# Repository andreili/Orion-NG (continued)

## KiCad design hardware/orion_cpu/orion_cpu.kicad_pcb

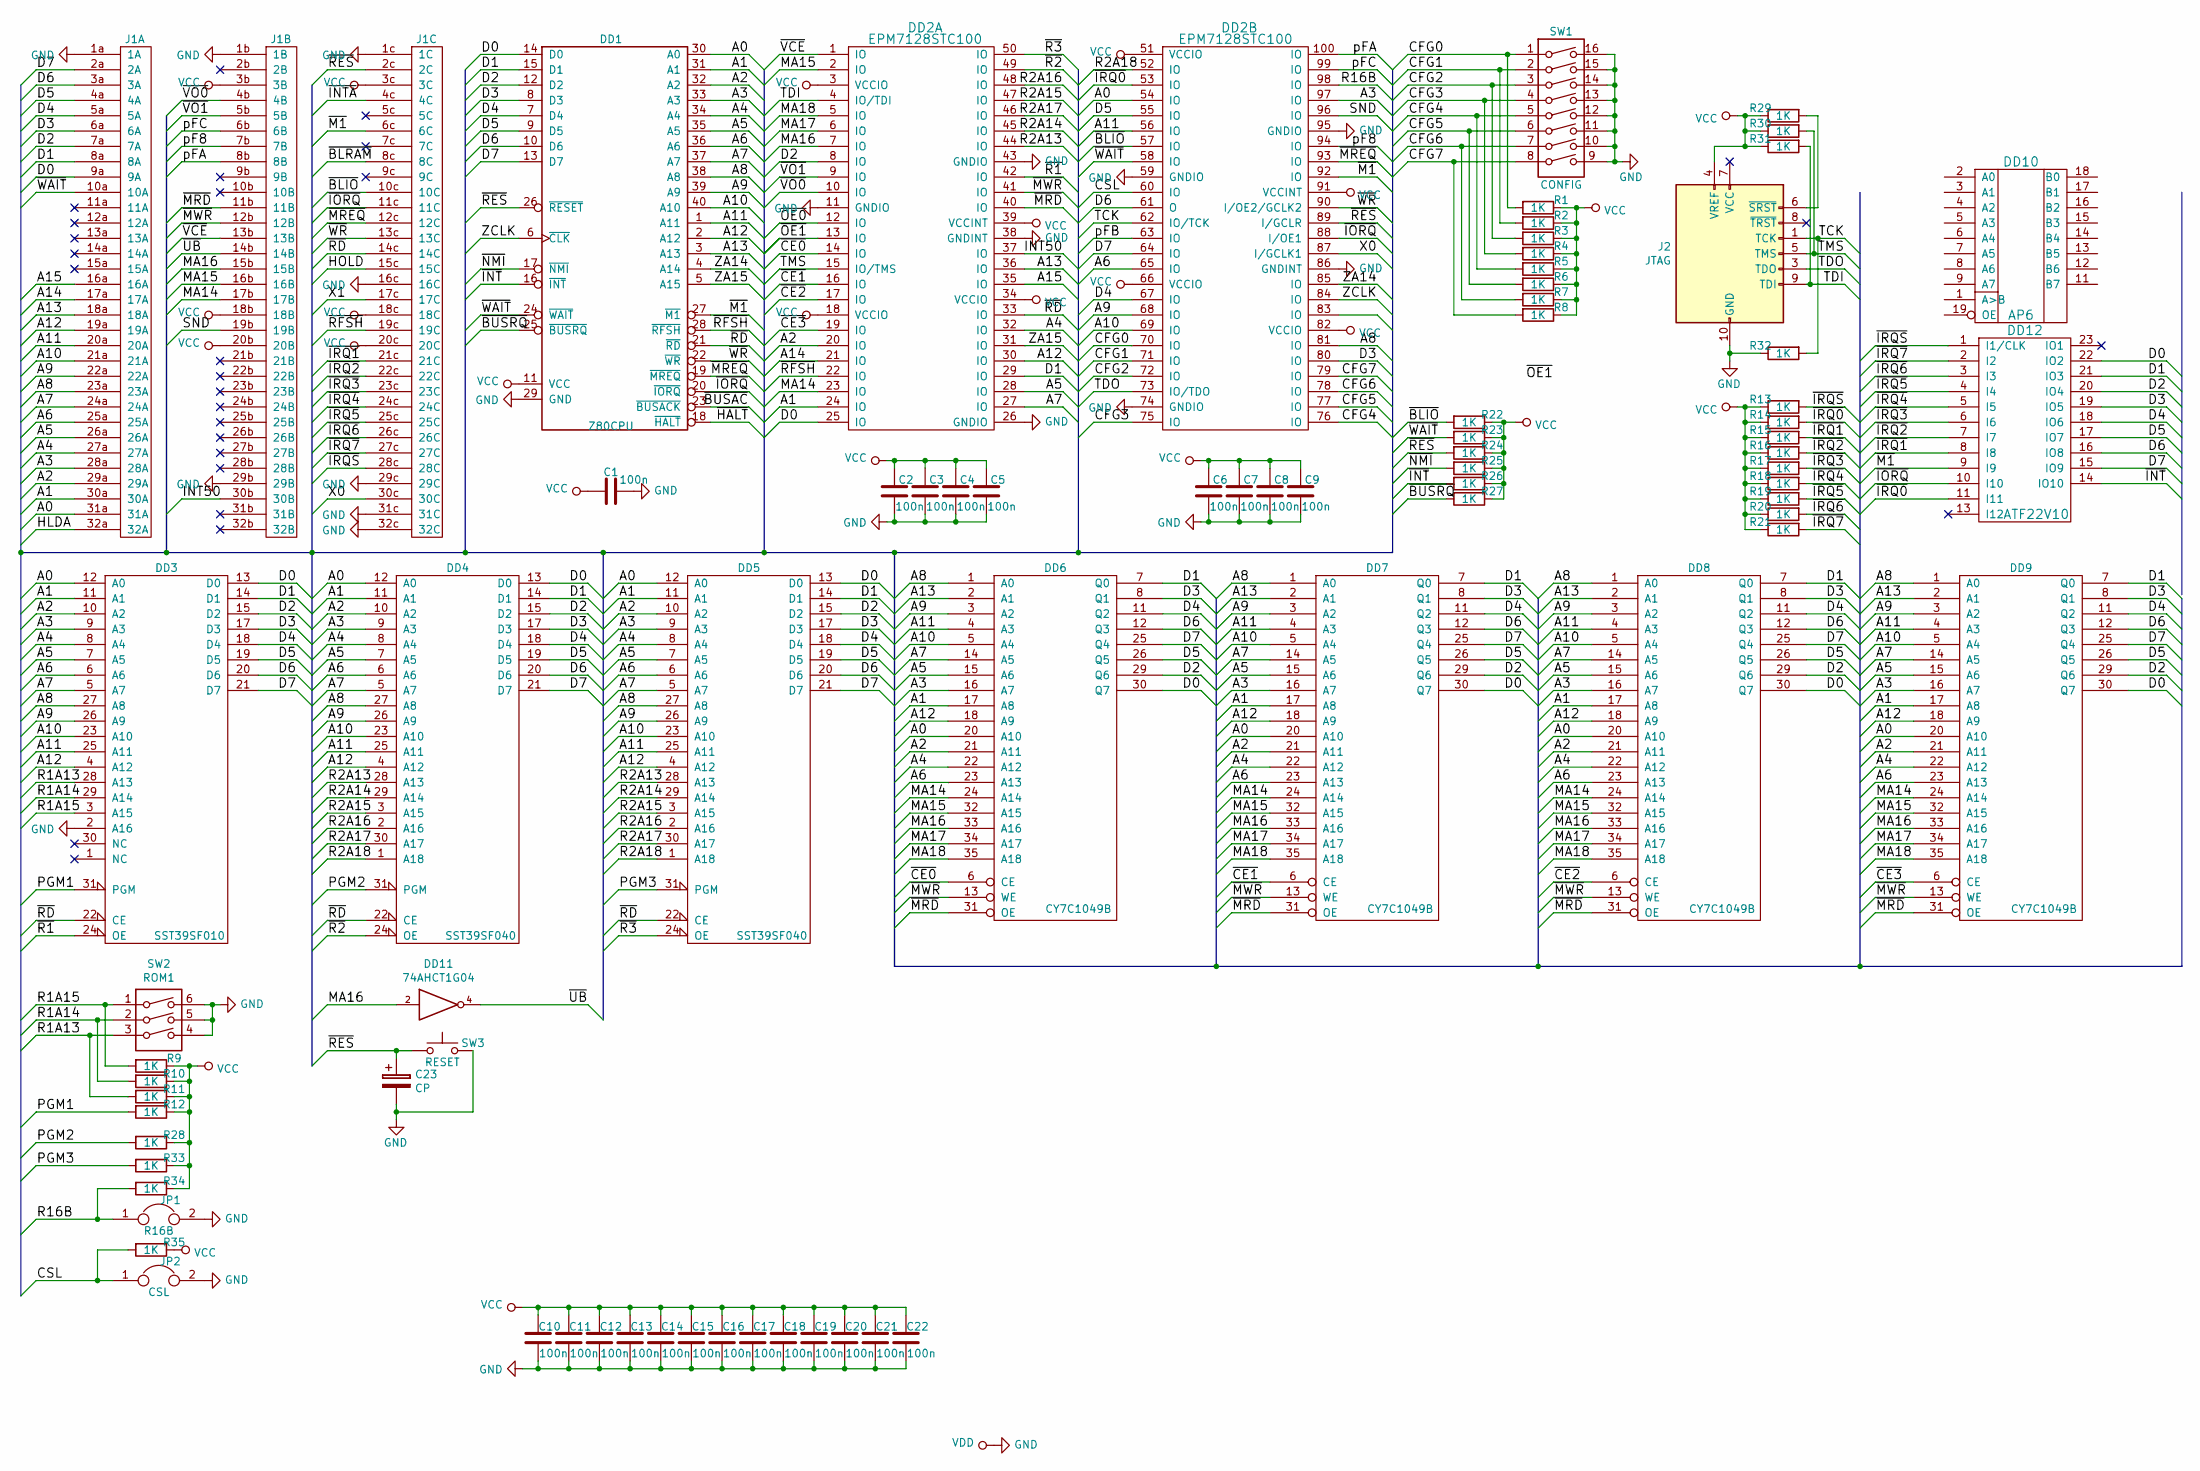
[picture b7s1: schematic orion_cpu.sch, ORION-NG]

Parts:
C1, C2, C3, C4, C5, C6, C7, C8, C9, C10, C11, C12, C13, C14, C15, C16, C17, C18, C19, C20, C21, C22: 100n; C_0805_2012Metric
C23: CP; CP_Tantalum_Case-A_EIA-3216-18_Hand
DD1: Z80CPU; DIP-40_W15.24mm_Socket
DD2: EPM7128STC100; LQFP-100_14x14mm_P0.5mm
DD3: SST39SF010; plcc32_pth-skt
DD4, DD5: SST39SF040; plcc32_pth-skt
DD6, DD7, DD8, DD9: CY7C1049B; SOJ-36
DD10: AP6; SOIC-20W_7.5x12.8mm_P1.27mm
DD11: 74AHCT1G04; SOT-353_SC-70-5_Handsoldering
DD12: ATF22V10; DIP-24_W7.62mm_Socket
J1: C96ABC; Socket_DIN41612-CaseC1-full-Male-96Pin-3rows
J2: JTAG; PinHeader_2x05_P2.54mm_Vertical
JP1: R16B; Pin_Header_Straight_1x02_Pitch2.54mm
JP2: CSL; Pin_Header_Straight_1x02_Pitch2.54mm
R1, R2, R3, R4, R5, R6, R7, R8, R9, R10, R11, R12, R13, R14, R15, R16, R17, R18, R19, R20, R21, R22, R23, R24, R25, R26, R27, R28, R29, R30, R31, R32, R33, R34, R35: 1K; R_0805_2012Metric
SW1: CONFIG; SW_DIP_SPSTx08_Slide_9.78x22.5mm_W7.62mm_P2.54mm
SW2: ROM1; SW_DIP_SPSTx03_Slide_9.78x9.8mm_W7.62mm_P2.54mm
SW3: RESET; SW_Tactile_SPST_Angled_PTS645Vx83-2LFS

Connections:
/A0: DD1.30 (A0), DD2.54 (IO), DD3.12 (A0), DD4.12 (A0), DD5.12 (A0), DD6.20 (A10), DD7.20 (A10), DD8.20 (A10), DD9.20 (A10), J1.31a (31A)
/A1: DD1.31 (A1), DD2.24 (IO), DD3.11 (A1), DD4.11 (A1), DD5.11 (A1), DD6.17 (A8), DD7.17 (A8), DD8.17 (A8), DD9.17 (A8), J1.30a (30A)
/A2: DD1.32 (A2), DD2.20 (IO), DD3.10 (A2), DD4.10 (A2), DD5.10 (A2), DD6.21 (A11), DD7.21 (A11), DD8.21 (A11), DD9.21 (A11), J1.29a (29A)
/A3: DD1.33 (A3), DD2.97 (IO), DD3.9 (A3), DD4.9 (A3), DD5.9 (A3), DD6.16 (A7), DD7.16 (A7), DD8.16 (A7), DD9.16 (A7), J1.28a (28A)
/A4: DD1.34 (A4), DD2.32 (IO), DD3.8 (A4), DD4.8 (A4), DD5.8 (A4), DD6.22 (A12), DD7.22 (A12), DD8.22 (A12), DD9.22 (A12), J1.27a (27A)
/A5: DD1.35 (A5), DD2.28 (IO), DD3.7 (A5), DD4.7 (A5), DD5.7 (A5), DD6.15 (A6), DD7.15 (A6), DD8.15 (A6), DD9.15 (A6), J1.26a (26A)
/A6: DD1.36 (A6), DD2.65 (IO), DD3.6 (A6), DD4.6 (A6), DD5.6 (A6), DD6.23 (A13), DD7.23 (A13), DD8.23 (A13), DD9.23 (A13), J1.25a (25A)
/A7: DD1.37 (A7), DD2.27 (IO), DD3.5 (A7), DD4.5 (A7), DD5.5 (A7), DD6.14 (A5), DD7.14 (A5), DD8.14 (A5), DD9.14 (A5), J1.24a (24A)
/A8: DD1.38 (A8), DD2.81 (IO), DD3.27 (A8), DD4.27 (A8), DD5.27 (A8), DD6.1 (A0), DD7.1 (A0), DD8.1 (A0), DD9.1 (A0), J1.23a (23A)
/A9: DD1.39 (A9), DD2.68 (IO), DD3.26 (A9), DD4.26 (A9), DD5.26 (A9), DD6.3 (A2), DD7.3 (A2), DD8.3 (A2), DD9.3 (A2), J1.22a (22A)
/A10: DD1.40 (A10), DD2.69 (IO), DD3.23 (A10), DD4.23 (A10), DD5.23 (A10), DD6.5 (A4), DD7.5 (A4), DD8.5 (A4), DD9.5 (A4), J1.21a (21A)
/A11: DD1.1 (A11), DD2.56 (IO), DD3.25 (A11), DD4.25 (A11), DD5.25 (A11), DD6.4 (A3), DD7.4 (A3), DD8.4 (A3), DD9.4 (A3), J1.20a (20A)
/A12: DD1.2 (A12), DD2.30 (IO), DD3.4 (A12), DD4.4 (A12), DD5.4 (A12), DD6.18 (A9), DD7.18 (A9), DD8.18 (A9), DD9.18 (A9), J1.19a (19A)
/A13: DD1.3 (A13), DD2.36 (IO), DD6.2 (A1), DD7.2 (A1), DD8.2 (A1), DD9.2 (A1), J1.18a (18A)
/A14: DD2.21 (IO), J1.17a (17A)
/A15: DD2.35 (IO), J1.16a (16A)
/CFG0: DD2.70 (IO), R1.2, SW1.1
/CFG1: DD2.71 (IO), R2.2, SW1.2
/CFG2: DD2.72 (IO), R3.2, SW1.3
/CFG3: DD2.75 (IO), R4.2, SW1.4
/CFG4: DD2.76 (IO), R5.2, SW1.5
/CFG5: DD2.77 (IO), R6.2, SW1.6
/CFG6: DD2.78 (IO), R7.2, SW1.7
/CFG7: DD2.79 (IO), R8.2, SW1.8
/CSL: DD2.60 (IO), JP2.1, R35.2
/D0: DD1.14 (D0), DD2.25 (IO), DD3.13 (D0), DD4.13 (D0), DD5.13 (D0), DD6.30 (Q7), DD7.30 (Q7), DD8.30 (Q7), DD9.30 (Q7), DD12.22 (IO2), J1.9a (9A)
/D1: DD1.15 (D1), DD2.29 (IO), DD3.14 (D1), DD4.14 (D1), DD5.14 (D1), DD6.7 (Q0), DD7.7 (Q0), DD8.7 (Q0), DD9.7 (Q0), DD12.21 (IO3), J1.8a (8A)
/D2: DD1.12 (D2), DD2.8 (IO), DD3.15 (D2), DD4.15 (D2), DD5.15 (D2), DD6.29 (Q6), DD7.29 (Q6), DD8.29 (Q6), DD9.29 (Q6), DD12.20 (IO4), J1.7a (7A)
/D3: DD1.8 (D3), DD2.80 (IO), DD3.17 (D3), DD4.17 (D3), DD5.17 (D3), DD6.8 (Q1), DD7.8 (Q1), DD8.8 (Q1), DD9.8 (Q1), DD12.19 (IO5), J1.6a (6A)
/D4: DD1.7 (D4), DD2.67 (IO), DD3.18 (D4), DD4.18 (D4), DD5.18 (D4), DD6.11 (Q2), DD7.11 (Q2), DD8.11 (Q2), DD9.11 (Q2), DD12.18 (IO6), J1.5a (5A)
/D5: DD1.9 (D5), DD2.55 (IO), DD3.19 (D5), DD4.19 (D5), DD5.19 (D5), DD6.26 (Q5), DD7.26 (Q5), DD8.26 (Q5), DD9.26 (Q5), DD12.17 (IO7), J1.4a (4A)
/D6: DD1.10 (D6), DD2.61 (O), DD3.20 (D6), DD4.20 (D6), DD5.20 (D6), DD6.12 (Q3), DD7.12 (Q3), DD8.12 (Q3), DD9.12 (Q3), DD12.16 (IO8), J1.3a (3A)
/D7: DD1.13 (D7), DD2.64 (IO), DD3.21 (D7), DD4.21 (D7), DD5.21 (D7), DD6.25 (Q4), DD7.25 (Q4), DD8.25 (Q4), DD9.25 (Q4), DD12.15 (IO9), J1.2a (2A)
/HLDA: J1.32a (32A)
/HOLD: J1.15c (15C)
/INT50: DD2.37 (IO), J1.30b (30B)
/MA14: DD2.23 (IO), DD6.24 (A14), DD7.24 (A14), DD8.24 (A14), DD9.24 (A14), J1.17b (17B)
/MA15: DD2.2 (IO), DD6.32 (A15), DD7.32 (A15), DD8.32 (A15), DD9.32 (A15), J1.16b (16B)
/MA16: DD2.7 (IO), DD6.33 (A16), DD7.33 (A16), DD8.33 (A16), DD9.33 (A16), DD11.2, J1.15b (15B)
/MA17: DD2.6 (IO), DD6.34 (A17), DD7.34 (A17), DD8.34 (A17), DD9.34 (A17)
/MA18: DD2.5 (IO), DD6.35 (A18), DD7.35 (A18), DD8.35 (A18), DD9.35 (A18)
/PGM1: DD3.31 (PGM), R12.2
/PGM2: DD4.31 (PGM), R28.2
/PGM3: DD5.31 (PGM), R33.2
/R1A13: DD3.28 (A13), R11.2, SW2.3
/R1A14: DD3.29 (A14), R10.2, SW2.2
/R1A15: DD3.3 (A15), R9.2, SW2.1
/R2A13: DD2.44 (IO), DD4.28 (A13), DD5.28 (A13)
/R2A14: DD2.45 (IO), DD4.29 (A14), DD5.29 (A14)
/R2A15: DD2.47 (IO), DD4.3 (A15), DD5.3 (A15)
/R2A16: DD2.48 (IO), DD4.2 (A16), DD5.2 (A16)
/R2A17: DD2.46 (IO), DD4.30 (A17), DD5.30 (A17)
/R2A18: DD2.52 (IO), DD4.1 (A18), DD5.1 (A18)
/R16B: DD2.98 (IO), JP1.1, R34.2
/SND: DD2.96 (IO), J1.19b (19B)
/TCK: DD2.62 (IO/TCK), J2.1 (TCK), R32.2
/TDI: DD2.4 (IO/TDI), J2.9 (TDI), R31.2
/TDO: DD2.73 (IO/TDO), J2.3 (TDO)
/TMS: DD2.15 (IO/TMS), J2.5 (TMS), R30.2
/X0: DD2.87 (I/GCLK1), J1.30c (30C)
/X1: J1.17c (17C)
/ZA14: DD1.4 (A14), DD2.85 (IO)
/ZA15: DD1.5 (A15), DD2.31 (IO)
/ZCLK: DD1.6 (~CLK~), DD2.84 (IO)
/pF8: DD2.94 (IO), J1.7b (7B)
/pFA: DD2.100 (IO), J1.8b (8B)
/pFB: DD2.63 (IO)
/pFC: DD2.99 (IO), J1.6b (6B)
/~BLIO: DD2.57 (IO), J1.10c (10C), R22.2
/~BLRAM: J1.8c (8C)
/~BUSAC: DD1.23 (~BUSACK~)
/~BUSRQ: DD1.25 (~BUSRQ~), R27.2
/~CE0: DD2.14 (IO), DD6.6 (CE)
/~CE1: DD2.16 (IO), DD7.6 (CE)
/~CE2: DD2.17 (IO), DD8.6 (CE)
/~CE3: DD2.19 (IO), DD9.6 (CE)
/~HALT: DD1.18 (~HALT~)
/~INT: DD1.16 (~INT~), DD12.14 (IO10), R26.2
/~INTA: J1.4c (4C)
/~IORQ: DD1.20 (~IORQ~), DD2.88 (I/OE1), DD12.10 (I10), J1.11c (11C)
/~IRQ0: DD2.53 (IO), DD12.11 (I11), R14.2
/~IRQ1: DD12.8 (I8), J1.21c (21C), R15.2
/~IRQ2: DD12.7 (I7), J1.22c (22C), R16.2
/~IRQ3: DD12.6 (I6), J1.23c (23C), R17.2
/~IRQ4: DD12.5 (I5), J1.24c (24C), R18.2
/~IRQ5: DD12.4 (I4), J1.25c (25C), R19.2
/~IRQ6: DD12.3 (I3), J1.26c (26C), R20.2
/~IRQ7: DD12.2 (I2), J1.27c (27C), R21.2
/~IRQS: DD12.1 (I1/CLK), J1.28c (28C), R13.2
/~M1: DD1.27 (~M1~), DD2.92 (IO), DD12.9 (I9), J1.6c (6C)
/~MRD: DD2.40 (IO), DD6.31 (OE), DD7.31 (OE), DD8.31 (OE), DD9.31 (OE), J1.11b (11B)
/~MREQ: DD1.19 (~MREQ~), DD2.93 (IO), J1.12c (12C)
/~MWR: DD2.41 (IO), DD6.13 (WE), DD7.13 (WE), DD8.13 (WE), DD9.13 (WE), J1.12b (12B)
/~NMI: DD1.17 (~NMI~), R25.2
/~OE0: DD2.12 (IO)
/~OE1: DD2.13 (IO)
/~R1: DD2.42 (IO), DD3.24 (OE)
/~R2: DD2.49 (IO), DD4.24 (OE)
/~R3: DD2.50 (IO), DD5.24 (OE)
/~RD: DD1.21 (~RD~), DD2.33 (IO), DD3.22 (CE), DD4.22 (CE), DD5.22 (CE), J1.14c (14C)
/~RES: C23.1, DD1.26 (~RESET~), DD2.89 (I/GCLR), J1.2c (2C), R24.2, SW3.2
/~RFSH: DD1.28 (~RFSH~), DD2.22 (IO), J1.19c (19C)
/~UB: DD11.4, J1.14b (14B)
/~VCE: DD2.1 (IO), J1.13b (13B)
/~VO0: DD2.10 (IO), J1.4b (4B)
/~VO1: DD2.9 (IO), J1.5b (5B)
/~WAIT: DD1.24 (~WAIT~), DD2.58 (IO), J1.10a (10A), R23.2
/~WR: DD1.22 (~WR~), DD2.90 (I/OE2/GCLK2), J1.13c (13C)
GND: C1.1, C2.1, C3.1, C4.1, C5.1, C6.1, C7.1, C8.1, C9.1, C10.1, C11.1, C12.1, C13.1, C14.1, C15.1, C16.1, C17.1, C18.1, C19.1, C20.1, C21.1, C22.1, C23.2, DD1.29 (GND), DD2.11 (GNDIO), DD2.26 (GNDIO), DD2.38 (GNDINT), DD2.43 (GNDIO), DD2.59 (GNDIO), DD2.74 (GNDIO), DD2.86 (GNDINT), DD2.95 (GNDIO), DD3.2 (A16), DD3.16 (GND), DD4.16 (GND), DD5.16 (GND), DD6.10 (VDD), DD6.28 (VDD), DD7.10 (VDD), DD7.28 (VDD), DD8.10 (VDD), DD8.28 (VDD), DD9.10 (VDD), DD9.28 (VDD), DD11.3 (GND), DD12.12 (GND), J1.1a (1A), J1.1b (1B), J1.1c (1C), J1.16c (16C), J1.29b (29B), J1.29c (29C), J1.31c (31C), J1.32c (32C), J2.2 (GND), J2.10 (GND), JP1.2, JP2.2, R32.1, SW1.9, SW1.10, SW1.11, SW1.12, SW1.13, SW1.14, SW1.15, SW1.16, SW2.4, SW2.5, SW2.6, SW3.1
unnamed: J2.6 (~SRST), R29.2
VCC: C1.2, C2.2, C3.2, C4.2, C5.2, C6.2, C7.2, C8.2, C9.2, C10.2, C11.2, C12.2, C13.2, C14.2, C15.2, C16.2, C17.2, C18.2, C19.2, C20.2, C21.2, C22.2, DD1.11 (VCC), DD2.3 (VCCIO), DD2.18 (VCCIO), DD2.34 (VCCIO), DD2.39 (VCCINT), DD2.51 (VCCIO), DD2.66 (VCCIO), DD2.82 (VCCIO), DD2.91 (VCCINT), DD3.32 (VCC), DD4.32 (VCC), DD5.32 (VCC), DD6.9 (VCC), DD6.27 (VCC), DD7.9 (VCC), DD7.27 (VCC), DD8.9 (VCC), DD8.27 (VCC), DD9.9 (VCC), DD9.27 (VCC), DD11.5 (VCC), DD12.24 (VCC), J1.3b (3B), J1.3c (3C), J1.18b (18B), J1.18c (18C), J1.20b (20B), J1.20c (20C), J2.4 (VREF), R1.1, R2.1, R3.1, R4.1, R5.1, R6.1, R7.1, R8.1, R9.1, R10.1, R11.1, R12.1, R13.1, R14.1, R15.1, R16.1, R17.1, R18.1, R19.1, R20.1, R21.1, R22.1, R23.1, R24.1, R25.1, R26.1, R27.1, R28.1, R29.1, R30.1, R31.1, R33.1, R34.1, R35.1

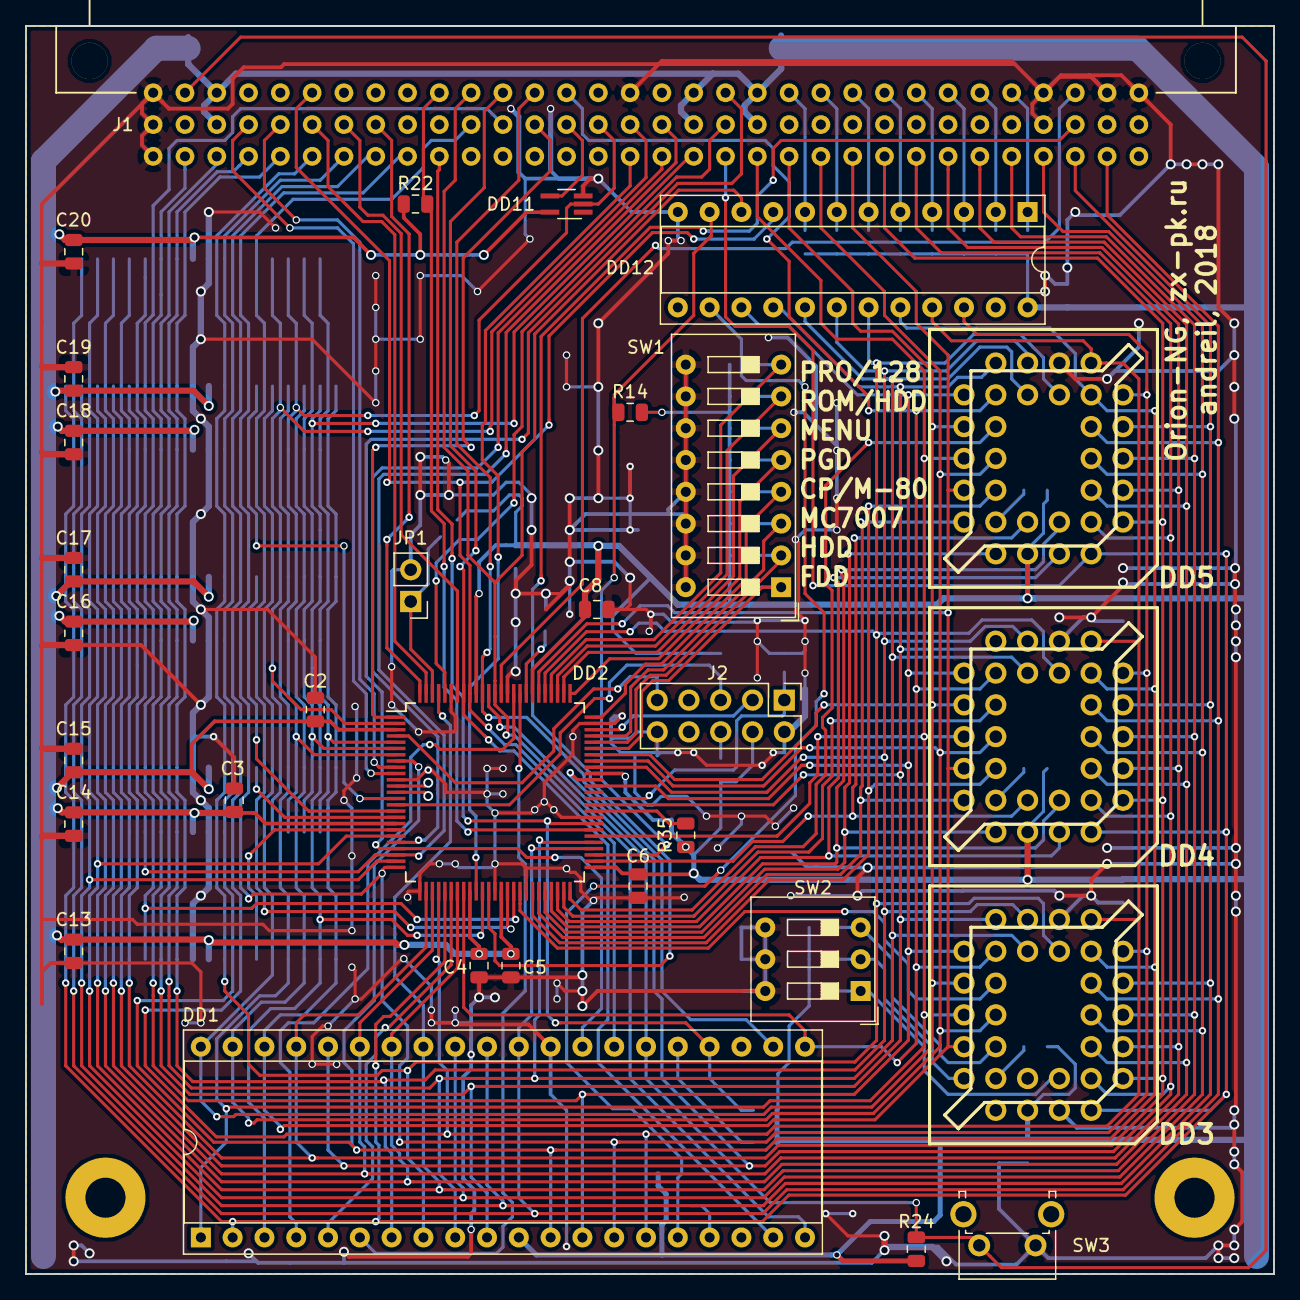
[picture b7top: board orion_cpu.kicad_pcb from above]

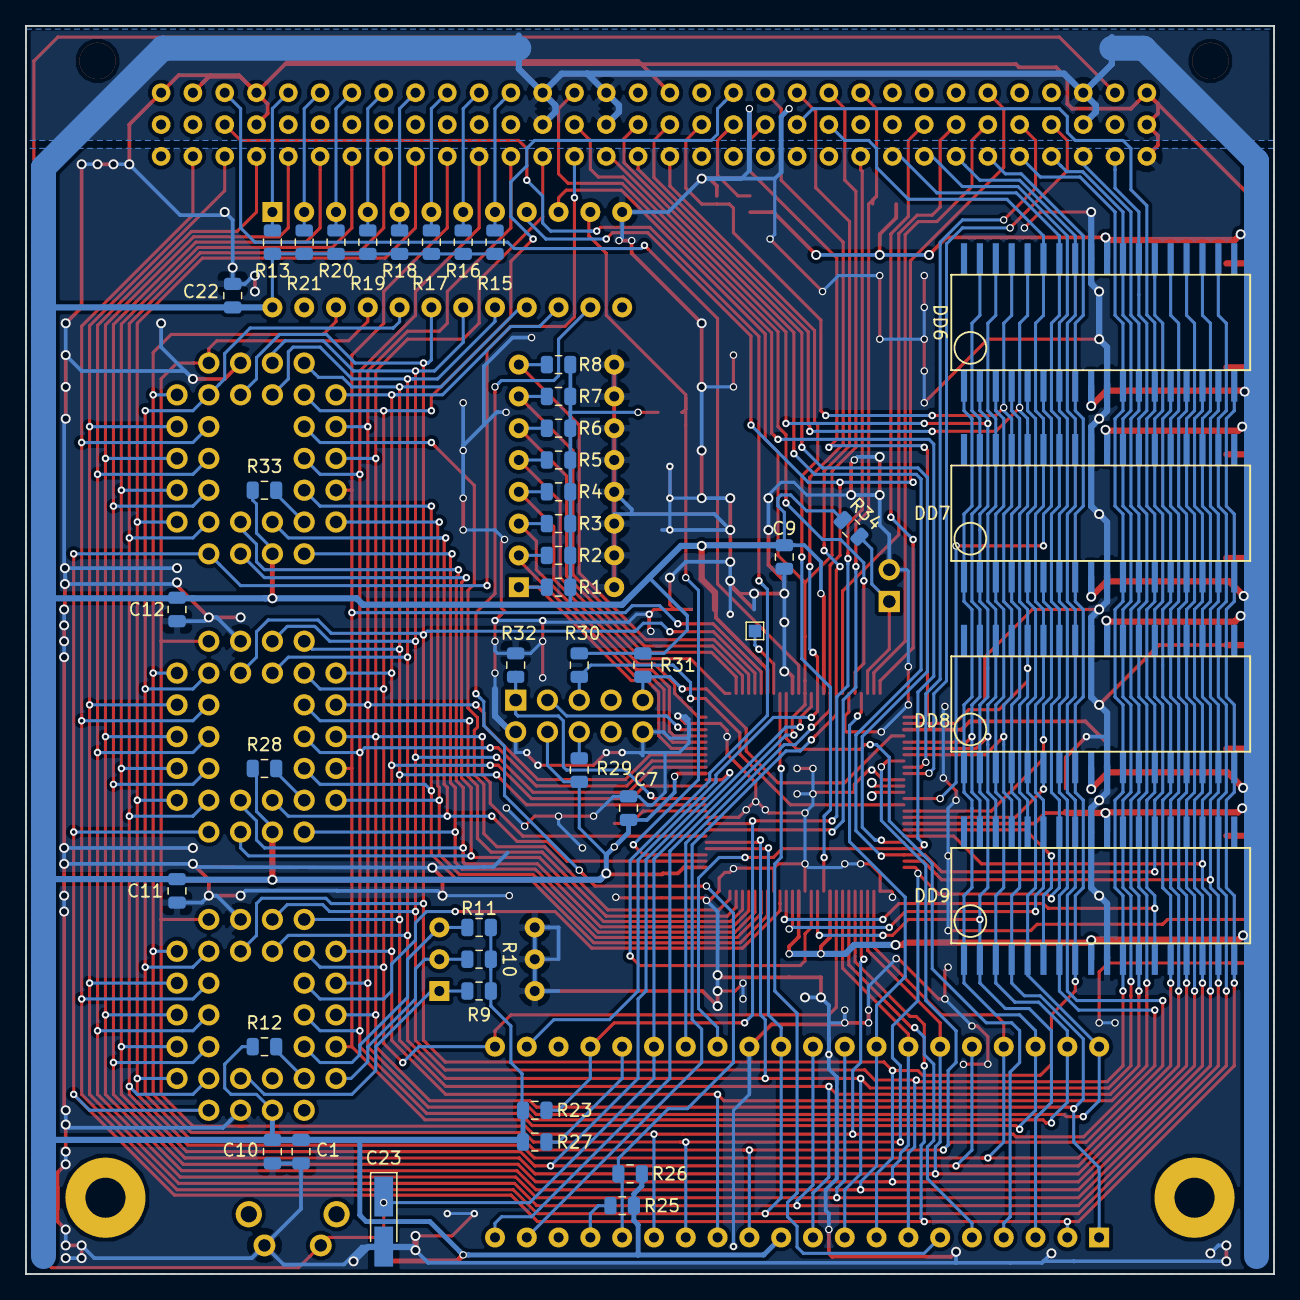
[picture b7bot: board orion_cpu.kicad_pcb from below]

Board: 2 copper layers, 99.7 x 99.7 mm, 74 parts (43 on the bottom side), 101 nets.

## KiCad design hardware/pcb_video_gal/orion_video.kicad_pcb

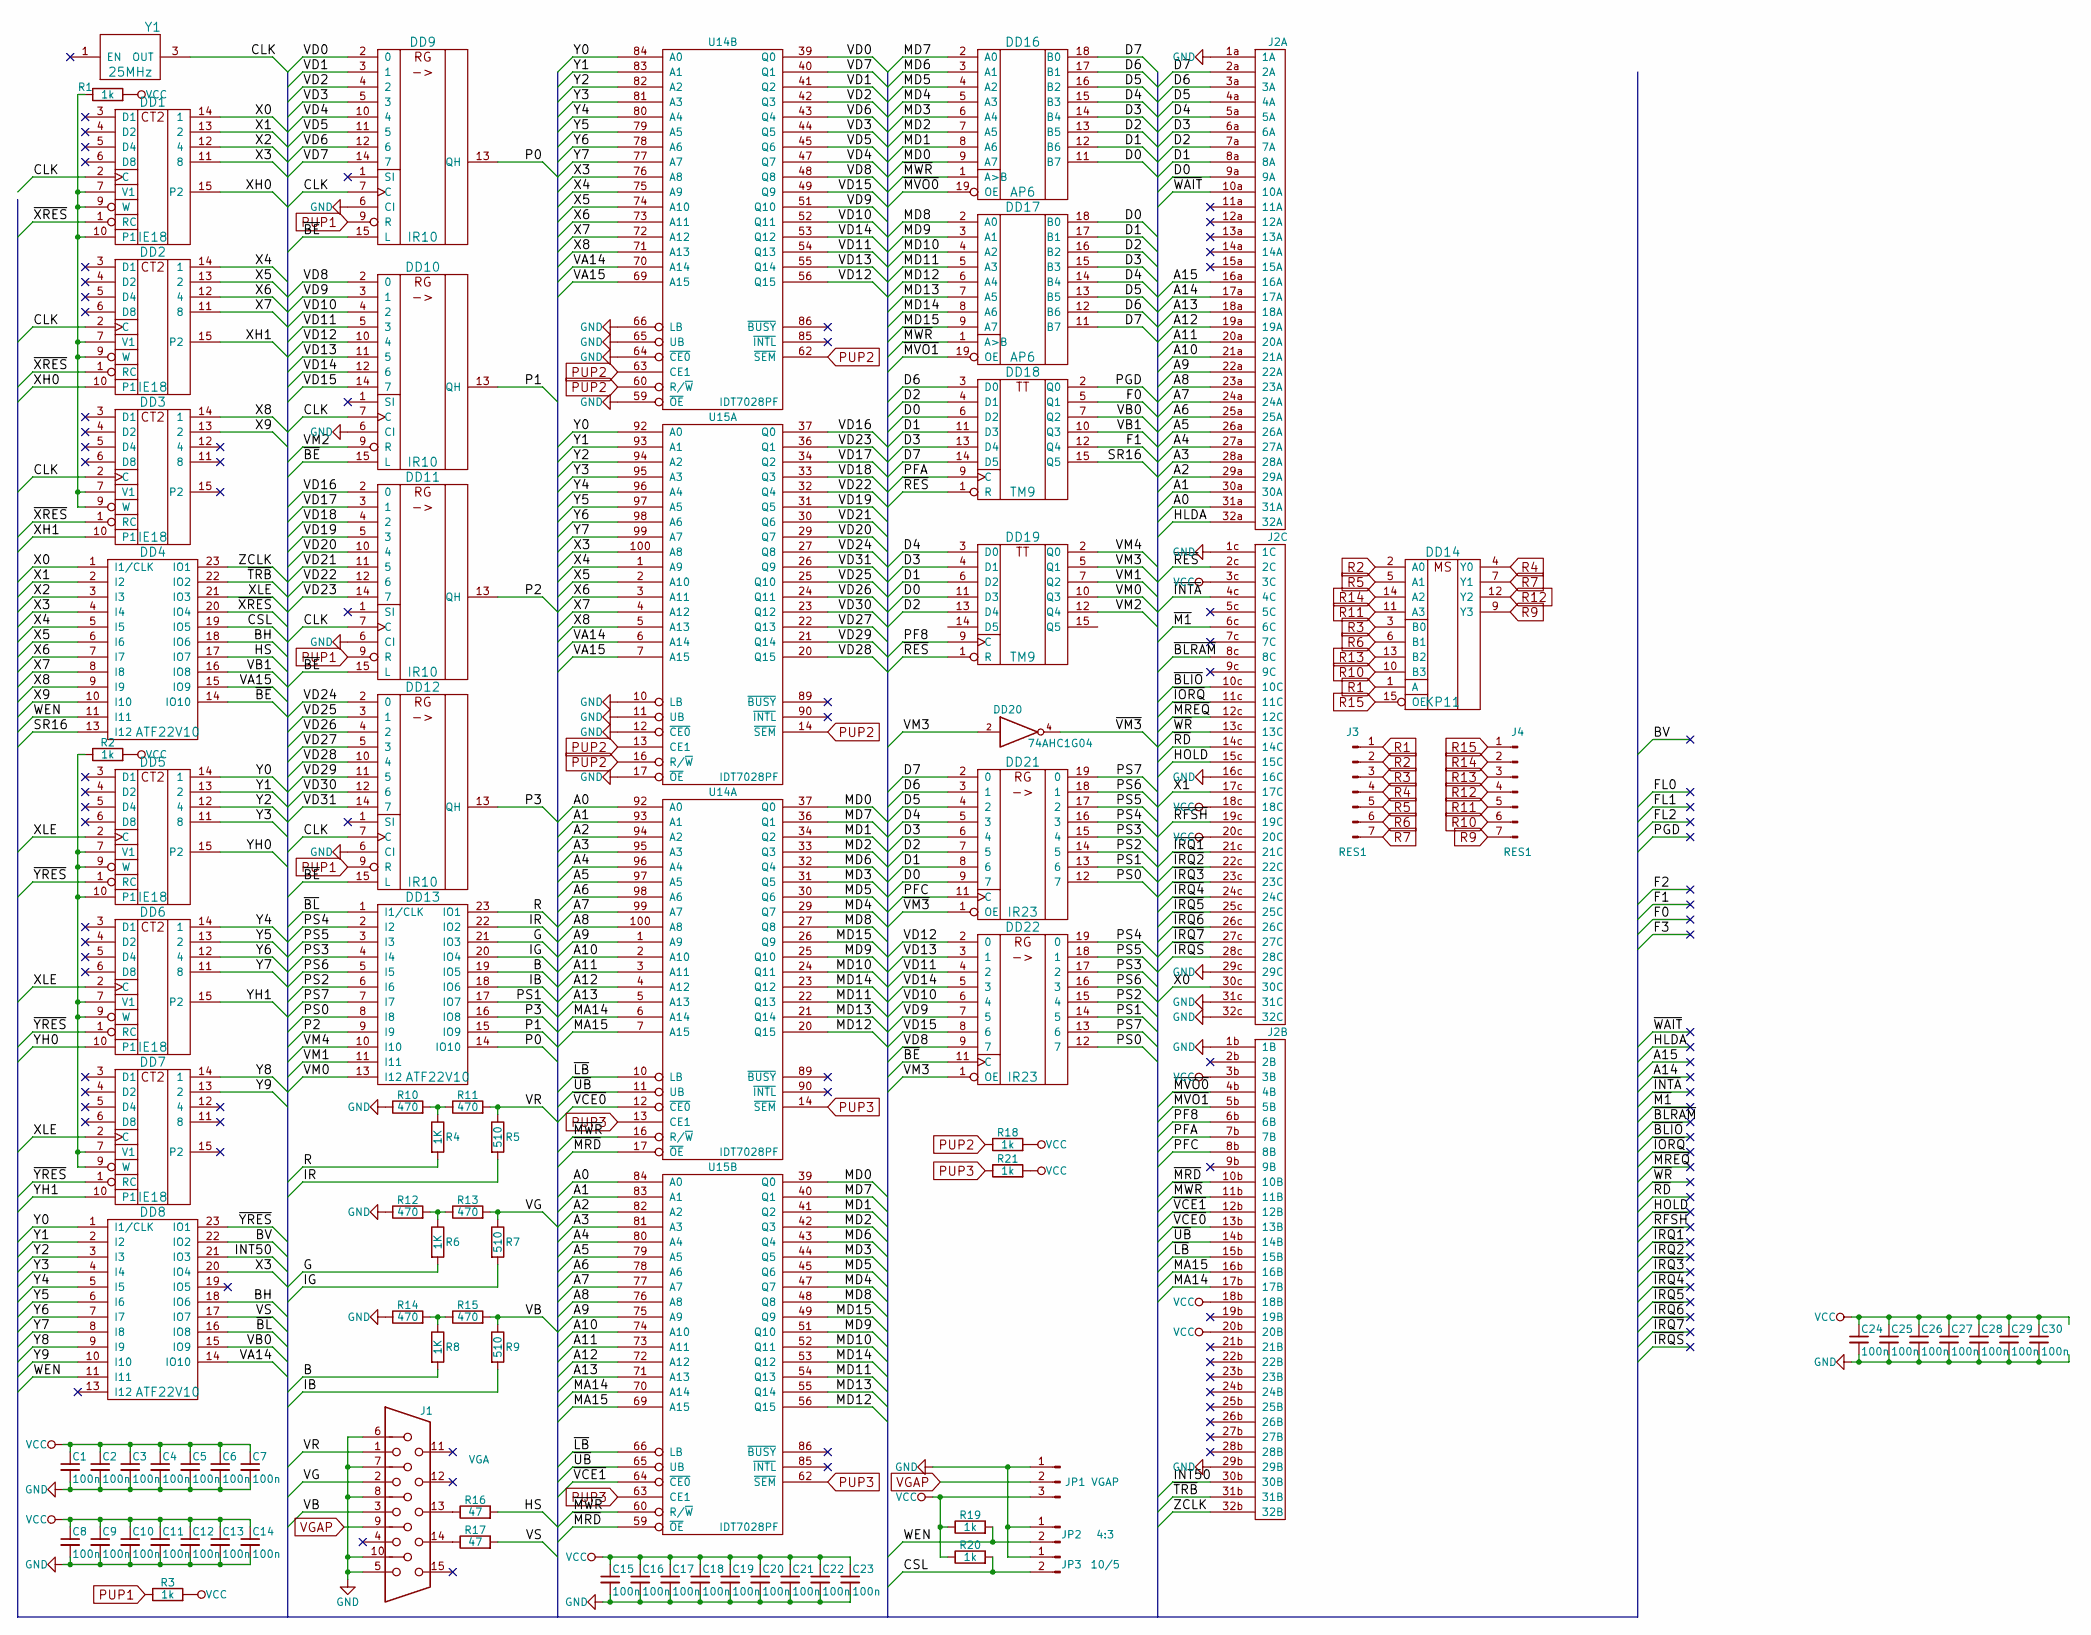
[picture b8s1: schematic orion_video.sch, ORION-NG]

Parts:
C1, C2, C3, C4, C5, C6, C7, C8, C9, C10, C11, C12, C13, C14, C15, C16, C17, C18, C19, C20, C21, C22, C23, C24, C25, C26, C27, C28, C29, C30: 100n; C_0805
DD1, DD2, DD3, DD5, DD6, DD7: IE18; SOIC-16_3.9x9.9mm_Pitch1.27mm
DD4, DD8: ATF22V10; DIP-24_W7.62mm
DD9, DD10, DD11, DD12: IR10; SOIC-16_3.9x9.9mm_Pitch1.27mm
DD13: ATF22V10; DIP-24_W7.62mm_LongPads
DD14: KP11; SOIC-16_3.9x9.9mm_Pitch1.27mm
DD16, DD17: AP6; SOIC-20W_7.5x12.8mm_Pitch1.27mm
DD18, DD19: TM9; SOIC-16_3.9x9.9mm_Pitch1.27mm
DD20: 74AHC1G04; SOT-353_SC-70-5_Handsoldering
DD21, DD22: IR23; SOIC-20W_7.5x12.8mm_Pitch1.27mm
J1: VGA; DB_15F-VGA
J2: C96ABC; Socket_DIN41612-CaseC1-full-Male-96Pin-3rows
J3, J4: RES1; Pin_Header_Straight_1x07_Pitch1.27mm
JP1: VGAP; Socket_Strip_Straight_1x03_Pitch2.54mm
JP2: 4:3; Socket_Strip_Straight_1x02_Pitch2.54mm
JP3: 10/5; Socket_Strip_Straight_1x02_Pitch2.54mm
R1, R2, R3, R18, R19, R20, R21: 1k; R_0805
R4, R6, R8: 1K; R_0805
R5, R7, R9: 510; R_0805
R10, R11, R12, R13, R14, R15: 470; R_0805
R16, R17: 47; R_0805
U14, U15: IDT7028PF; TQFP-100_14x14mm_Pitch0.5mm
Y1: 25MHz; Crystal_SMD_7050-4pin_7.0x5.0mm

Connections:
/A0: J2.31a (31A), U14.92 (A0), U15.84 (A0)
/A1: J2.30a (30A), U14.93 (A1), U15.83 (A1)
/A2: J2.29a (29A), U14.94 (A2), U15.82 (A2)
/A3: J2.28a (28A), U14.95 (A3), U15.81 (A3)
/A4: J2.27a (27A), U14.96 (A4), U15.80 (A4)
/A5: J2.26a (26A), U14.97 (A5), U15.79 (A5)
/A6: J2.25a (25A), U14.98 (A6), U15.78 (A6)
/A7: J2.24a (24A), U14.99 (A7), U15.77 (A7)
/A8: J2.23a (23A), U14.100 (A8), U15.76 (A8)
/A9: J2.22a (22A), U14.1 (A9), U15.75 (A9)
/A10: J2.21a (21A), U14.2 (A10), U15.74 (A10)
/A11: J2.20a (20A), U14.3 (A11), U15.73 (A11)
/A12: J2.19a (19A), U14.4 (A12), U15.72 (A12)
/A13: J2.18a (18A), U14.5 (A13), U15.71 (A13)
/A14: J2.17a (17A)
/A15: J2.16a (16A)
/B: DD13.19 (IO5), R8.2
/BH: DD4.18 (IO6), DD8.18 (IO6)
/BV: DD8.22 (IO2)
/CLK: DD1.2 (C), DD2.2 (C), DD3.2 (C), DD9.7 (C), DD10.7 (C), DD11.7 (C), DD12.7 (C), Y1.3 (OUT)
/CSL: DD4.19 (IO5), JP3.2, R20.2
/D0: DD16.11 (B7), DD17.18 (B0), DD18.6 (D2), DD19.11 (D3), DD21.9 (7), J2.9a (9A)
/D1: DD16.12 (B6), DD17.17 (B1), DD18.11 (D3), DD19.6 (D2), DD21.8 (6), J2.8a (8A)
/D2: DD16.13 (B5), DD17.16 (B2), DD18.4 (D1), DD19.13 (D4), DD21.7 (5), J2.7a (7A)
/D3: DD16.14 (B4), DD17.15 (B3), DD18.13 (D4), DD19.4 (D1), DD21.6 (4), J2.6a (6A)
/D4: DD16.15 (B3), DD17.14 (B4), DD19.3 (D0), DD21.5 (3), J2.5a (5A)
/D5: DD16.16 (B2), DD17.13 (B5), DD21.4 (2), J2.4a (4A)
/D6: DD16.17 (B1), DD17.12 (B6), DD18.3 (D0), DD21.3 (1), J2.3a (3A)
/D7: DD16.18 (B0), DD17.11 (B7), DD18.14 (D5), DD21.2 (0), J2.2a (2A)
/F0: DD18.5 (Q1)
/F1: DD18.12 (Q4)
/G: DD13.21 (IO3), R6.2
/HLDA: J2.32a (32A)
/HOLD: J2.15c (15C)
/HS: DD4.17 (IO7), R16.2
/IB: DD13.18 (IO6), R9.2
/IG: DD13.20 (IO4), R7.2
/INT50: DD8.21 (IO3), J2.30b (30B)
/IR: DD13.22 (IO2), R5.2
/MA14: J2.17b (17B), U14.6 (A14), U15.70 (A14)
/MA15: J2.16b (16B), U14.7 (A15), U15.69 (A15)
/MD0: DD16.9 (A7), U14.37 (Q0), U15.39 (Q0)
/MD1: DD16.8 (A6), U14.34 (Q2), U15.41 (Q2)
/MD2: DD16.7 (A5), U14.33 (Q3), U15.42 (Q3)
/MD3: DD16.6 (A4), U14.31 (Q5), U15.44 (Q5)
/MD4: DD16.5 (A3), U14.29 (Q7), U15.47 (Q7)
/MD5: DD16.4 (A2), U14.30 (Q6), U15.45 (Q6)
/MD6: DD16.3 (A1), U14.32 (Q4), U15.43 (Q4)
/MD7: DD16.2 (A0), U14.36 (Q1), U15.40 (Q1)
/MD8: DD17.2 (A0), U14.27 (Q8), U15.48 (Q8)
/MD9: DD17.3 (A1), U14.25 (Q10), U15.51 (Q10)
/MD10: DD17.4 (A2), U14.24 (Q11), U15.52 (Q11)
/MD11: DD17.5 (A3), U14.22 (Q13), U15.54 (Q13)
/MD12: DD17.6 (A4), U14.20 (Q15), U15.56 (Q15)
/MD13: DD17.7 (A5), U14.21 (Q14), U15.55 (Q14)
/MD14: DD17.8 (A6), U14.23 (Q12), U15.53 (Q12)
/MD15: DD17.9 (A7), U14.26 (Q9), U15.49 (Q9)
/P0: DD9.13 (QH), DD13.14 (IO10)
/P1: DD10.13 (QH), DD13.15 (IO9)
/P2: DD11.13 (QH), DD13.9 (I9)
/P3: DD12.13 (QH), DD13.16 (IO8)
/PF8: DD19.9 (C), J2.6b (6B)
/PFA: DD18.9 (C), J2.7b (7B)
/PFC: DD21.11 (C), J2.8b (8B)
/PGD: DD18.2 (Q0)
/PS0: DD13.8 (I8), DD21.12 (7), DD22.12 (7)
/PS1: DD13.17 (IO7), DD21.13 (6), DD22.14 (5)
/PS2: DD13.6 (I6), DD21.14 (5), DD22.15 (4)
/PS3: DD13.4 (I4), DD21.15 (4), DD22.17 (2)
/PS4: DD13.2 (I2), DD21.16 (3), DD22.19 (0)
/PS5: DD13.3 (I3), DD21.17 (2), DD22.18 (1)
/PS6: DD13.5 (I5), DD21.18 (1), DD22.16 (3)
/PS7: DD13.7 (I7), DD21.19 (0), DD22.13 (6)
/R: DD13.23 (IO1), R4.2
/SR16: DD4.13 (I12), DD18.15 (Q5)
/VA14: DD8.14 (IO10), U14.70 (A14), U15.6 (A14)
/VA15: DD4.15 (IO9), U14.69 (A15), U15.7 (A15)
/VB: J1.3, R9.1, R15.2
/VB0: DD8.15 (IO9), DD18.7 (Q2)
/VB1: DD4.16 (IO8), DD18.10 (Q3)
/VD0: DD9.2 (0), U14.39 (Q0)
/VD1: DD9.3 (1), U14.41 (Q2)
/VD2: DD9.4 (2), U14.42 (Q3)
/VD3: DD9.5 (3), U14.44 (Q5)
/VD4: DD9.10 (4), U14.47 (Q7)
/VD5: DD9.11 (5), U14.45 (Q6)
/VD6: DD9.12 (6), U14.43 (Q4)
/VD7: DD9.14 (7), U14.40 (Q1)
/VD8: DD10.2 (0), DD22.9 (7), U14.48 (Q8)
/VD9: DD10.3 (1), DD22.7 (5), U14.51 (Q10)
/VD10: DD10.4 (2), DD22.6 (4), U14.52 (Q11)
/VD11: DD10.5 (3), DD22.4 (2), U14.54 (Q13)
/VD12: DD10.10 (4), DD22.2 (0), U14.56 (Q15)
/VD13: DD10.11 (5), DD22.3 (1), U14.55 (Q14)
/VD14: DD10.12 (6), DD22.5 (3), U14.53 (Q12)
/VD15: DD10.14 (7), DD22.8 (6), U14.49 (Q9)
/VD16: DD11.2 (0), U15.37 (Q0)
/VD17: DD11.3 (1), U15.34 (Q2)
/VD18: DD11.4 (2), U15.33 (Q3)
/VD19: DD11.5 (3), U15.31 (Q5)
/VD20: DD11.10 (4), U15.29 (Q7)
/VD21: DD11.11 (5), U15.30 (Q6)
/VD22: DD11.12 (6), U15.32 (Q4)
/VD23: DD11.14 (7), U15.36 (Q1)
/VD24: DD12.2 (0), U15.27 (Q8)
/VD25: DD12.3 (1), U15.25 (Q10)
/VD26: DD12.4 (2), U15.24 (Q11)
/VD27: DD12.5 (3), U15.22 (Q13)
/VD28: DD12.10 (4), U15.20 (Q15)
/VD29: DD12.11 (5), U15.21 (Q14)
/VD30: DD12.12 (6), U15.23 (Q12)
/VD31: DD12.14 (7), U15.26 (Q9)
/VG: J1.2, R7.1, R13.2
/VM0: DD13.13 (I12), DD19.10 (Q3)
/VM1: DD13.11 (I11), DD19.7 (Q2)
/VM2: DD10.9 (R), DD19.12 (Q4)
/VM3: DD19.5 (Q1), DD20.2, DD22.1 (OE)
/VM4: DD13.10 (I10), DD19.2 (Q0)
/VR: J1.1, R5.1, R11.2
/VS: DD8.17 (IO7), R17.2
/WEN: DD4.11 (I11), DD8.11 (I11), JP2.2, R19.2
/X0: DD1.14 (1), DD4.1 (I1/CLK), J2.30c (30C)
/X1: DD1.13 (2), DD4.2 (I2), J2.17c (17C)
/X2: DD1.12 (4), DD4.3 (I3)
/X3: DD1.11 (8), DD4.4 (I4), DD8.20 (IO4), U14.76 (A8), U15.100 (A8)
/X4: DD2.14 (1), DD4.5 (I5), U14.75 (A9), U15.1 (A9)
/X5: DD2.13 (2), DD4.6 (I6), U14.74 (A10), U15.2 (A10)
/X6: DD2.12 (4), DD4.7 (I7), U14.73 (A11), U15.3 (A11)
/X7: DD2.11 (8), DD4.8 (I8), U14.72 (A12), U15.4 (A12)
/X8: DD3.14 (1), DD4.9 (I9), U14.71 (A13), U15.5 (A13)
/X9: DD3.13 (2), DD4.10 (I10)
/XH0: DD1.15 (P2), DD2.10 (P1)
/XH1: DD2.15 (P2), DD3.10 (P1)
/XLE: DD4.21 (IO3), DD5.2 (C), DD6.2 (C), DD7.2 (C)
/Y0: DD5.14 (1), DD8.1 (I1/CLK), U14.84 (A0), U15.92 (A0)
/Y1: DD5.13 (2), DD8.2 (I2), U14.83 (A1), U15.93 (A1)
/Y2: DD5.12 (4), DD8.3 (I3), U14.82 (A2), U15.94 (A2)
/Y3: DD5.11 (8), DD8.4 (I4), U14.81 (A3), U15.95 (A3)
/Y4: DD6.14 (1), DD8.5 (I5), U14.80 (A4), U15.96 (A4)
/Y5: DD6.13 (2), DD8.6 (I6), U14.79 (A5), U15.97 (A5)
/Y6: DD6.12 (4), DD8.7 (I7), U14.78 (A6), U15.98 (A6)
/Y7: DD6.11 (8), DD8.8 (I8), U14.77 (A7), U15.99 (A7)
/Y8: DD7.14 (1), DD8.9 (I9)
/Y9: DD7.13 (2), DD8.10 (I10)
/YH0: DD5.15 (P2), DD6.10 (P1)
/YH1: DD6.15 (P2), DD7.10 (P1)
/ZCLK: DD4.23 (IO1), J2.32b (32B)
/~BE: DD4.14 (IO10), DD9.15 (L), DD10.15 (L), DD11.15 (L), DD12.15 (L), DD22.11 (C)
/~BL: DD8.16 (IO8), DD13.1 (I1/CLK)
/~BLIO: J2.10c (10C)
/~BLRAM: J2.8c (8C)
/~INTA: J2.4c (4C)
/~IORQ: J2.11c (11C)
/~IRQ1: J2.21c (21C)
/~IRQ2: J2.22c (22C)
/~IRQ3: J2.23c (23C)
/~IRQ4: J2.24c (24C)
/~IRQ5: J2.25c (25C)
/~IRQ6: J2.26c (26C)
/~IRQ7: J2.27c (27C)
/~IRQS: J2.28c (28C)
/~LB: J2.15b (15B), U14.10 (LB), U15.66 (LB)
/~M1: J2.6c (6C)
/~MRD: J2.10b (10B), U14.17 (~OE), U15.59 (~OE)
/~MREQ: J2.12c (12C)
/~MVO0: DD16.19 (OE), J2.4b (4B)
/~MVO1: DD17.19 (OE), J2.5b (5B)
/~MWR: DD16.1 (A>B), DD17.1 (A>B), J2.11b (11B), U14.16 (R/~W), U15.60 (R/~W)
/~RD: J2.14c (14C)
/~RES: DD18.1 (R), DD19.1 (R), J2.2c (2C)
/~RFSH: J2.19c (19C)
/~TRB: DD4.22 (IO2), J2.31b (31B)
/~UB: J2.14b (14B), U14.11 (UB), U15.65 (UB)
/~VCE0: J2.13b (13B), U14.12 (~CE0)
/~VCE1: J2.12b (12B), U15.64 (~CE0)
/~VM3: DD20.4, DD21.1 (OE)
/~WAIT: J2.10a (10A)
/~WR: J2.13c (13C)
/~XRES: DD1.1 (RC), DD2.1 (RC), DD3.1 (RC), DD4.20 (IO4)
/~YRES: DD5.1 (RC), DD6.1 (RC), DD7.1 (RC), DD8.23 (IO1)
GND: C1.2, C2.2, C3.2, C4.2, C5.2, C6.2, C7.2, C8.2, C9.2, C10.2, C11.2, C12.2, C13.2, C14.2, C15.2, C16.2, C17.2, C18.2, C19.2, C20.2, C21.2, C22.2, C23.2, C24.2, C25.2, C26.2, C27.2, C28.2, C29.2, C30.2, DD1.8 (GND), DD2.8 (GND), DD3.8 (GND), DD4.12 (GND), DD5.8 (GND), DD6.8 (GND), DD7.8 (GND), DD8.12 (GND), DD9.6 (CI), DD9.8 (GND), DD10.6 (CI), DD10.8 (GND), DD11.6 (CI), DD11.8 (GND), DD12.6 (CI), DD12.8 (GND), DD13.12 (GND), DD16.10 (GND), DD17.10 (GND), DD18.8 (GND), DD19.8 (GND), DD20.3 (GND), DD21.10 (GND), DD22.10 (GND), J1.5, J1.6, J1.7, J1.8, J1.10, J2.1a (1A), J2.1b (1B), J2.1c (1C), J2.16c (16C), J2.29b (29B), J2.29c (29C), J2.31c (31C), J2.32c (32C), JP1.1, JP2.1, JP3.1, R10.1, R12.1, R14.1, U14.18 (GND), U14.19 (GND), U14.35 (GND), U14.38 (GND), U14.57 (GND), U14.58 (GND), U14.59 (~OE), U14.61 (GND), U14.64 (~CE0), U14.65 (UB), U14.66 (LB), U14.88 (GND), U15.10 (LB), U15.11 (UB), U15.12 (~CE0), U15.17 (~OE), U15.18 (GND), U15.19 (GND), U15.35 (GND), U15.38 (GND), U15.57 (GND), U15.58 (GND), U15.61 (GND), U15.88 (GND), Y1.2 (GND); also elsewhere on the board
unnamed: DD1.7 (V1), DD1.9 (W), DD1.10 (P1), DD2.7 (V1), DD2.9 (W), DD3.7 (V1), DD3.9 (W), R1.1
unnamed: DD5.7 (V1), DD5.9 (W), DD5.10 (P1), DD6.7 (V1), DD6.9 (W), DD7.7 (V1), DD7.9 (W), R2.1
unnamed: J1.13, R16.1
unnamed: J1.14, R17.1
unnamed: R4.1, R10.2, R11.1
unnamed: R6.1, R12.2, R13.1
unnamed: R8.1, R14.2, R15.1
PUP1: DD9.9 (R), DD11.9 (R), DD12.9 (R), R3.1
PUP2: R18.1, U14.60 (R/~W), U14.62 (~SEM), U14.63 (CE1), U15.13 (CE1), U15.14 (~SEM), U15.16 (R/~W)
PUP3: R21.1, U14.13 (CE1), U14.14 (~SEM), U15.62 (~SEM), U15.63 (CE1)
R1: DD14.1 (A), J3.1; also elsewhere on the board
R2: DD14.2 (A0), J3.2; also elsewhere on the board
R3: DD14.3 (B0), J3.3; also elsewhere on the board
R4: DD14.4 (Y0), J3.4; also elsewhere on the board
R5: DD14.5 (A1), J3.5; also elsewhere on the board
R6: DD14.6 (B1), J3.6; also elsewhere on the board
R7: DD14.7 (Y1), J3.7; also elsewhere on the board
R9: DD14.9 (Y3), J4.7; also elsewhere on the board
R10: DD14.10 (B3), J4.6; also elsewhere on the board
R11: DD14.11 (A3), J4.5; also elsewhere on the board
R12: DD14.12 (Y2), J4.4; also elsewhere on the board
R13: DD14.13 (B2), J4.3; also elsewhere on the board
R14: DD14.14 (A2), J4.2; also elsewhere on the board
R15: DD14.15 (OE), J4.1; also elsewhere on the board
VCC: C1.1, C2.1, C3.1, C4.1, C5.1, C6.1, C7.1, C8.1, C9.1, C10.1, C11.1, C12.1, C13.1, C14.1, C15.1, C16.1, C17.1, C18.1, C19.1, C20.1, C21.1, C22.1, C23.1, C24.1, C25.1, C26.1, C27.1, C28.1, C29.1, C30.1, DD1.16 (VCC), DD2.16 (VCC), DD3.16 (VCC), DD4.24 (VCC), DD5.16 (VCC), DD6.16 (VCC), DD7.16 (VCC), DD8.24 (VCC), DD9.16 (VCC), DD10.16 (VCC), DD11.16 (VCC), DD12.16 (VCC), DD13.24 (VCC), DD16.20 (VCC), DD17.20 (VCC), DD18.16 (VCC), DD19.16 (VCC), DD20.5 (VCC), DD21.20 (VCC), DD22.20 (VCC), J2.3b (3B), J2.3c (3C), J2.18b (18B), J2.18c (18C), J2.20b (20B), J2.20c (20C), JP1.3, R1.2, R2.2, R3.2, R18.2, R19.1, R20.1, R21.2, U14.15 (VCC), U14.28 (VCC), U14.46 (VCC), U15.15 (VCC), U15.28 (VCC), U15.46 (VCC), Y1.4 (VCC); also elsewhere on the board
VGAP: J1.9, JP1.2
